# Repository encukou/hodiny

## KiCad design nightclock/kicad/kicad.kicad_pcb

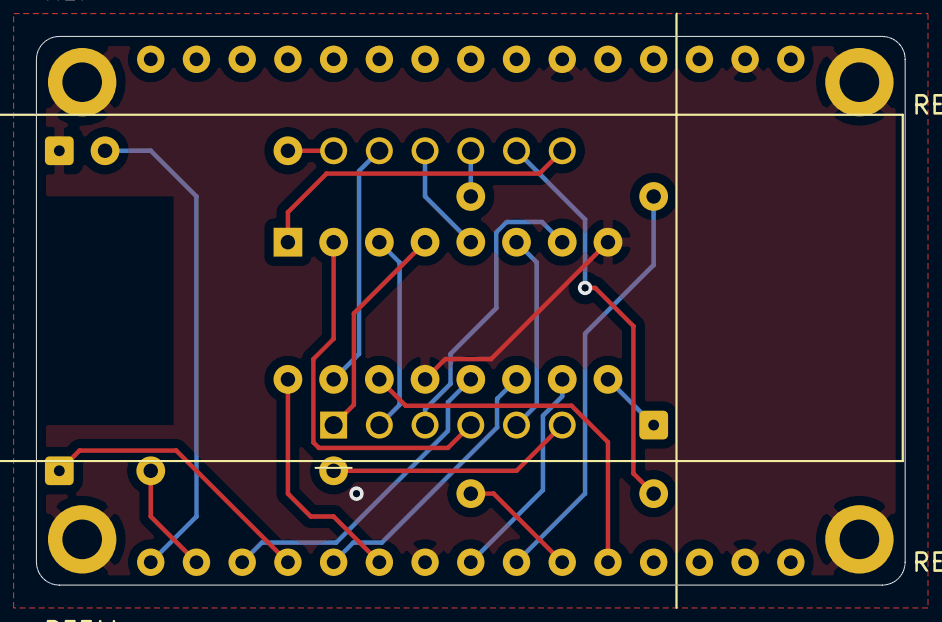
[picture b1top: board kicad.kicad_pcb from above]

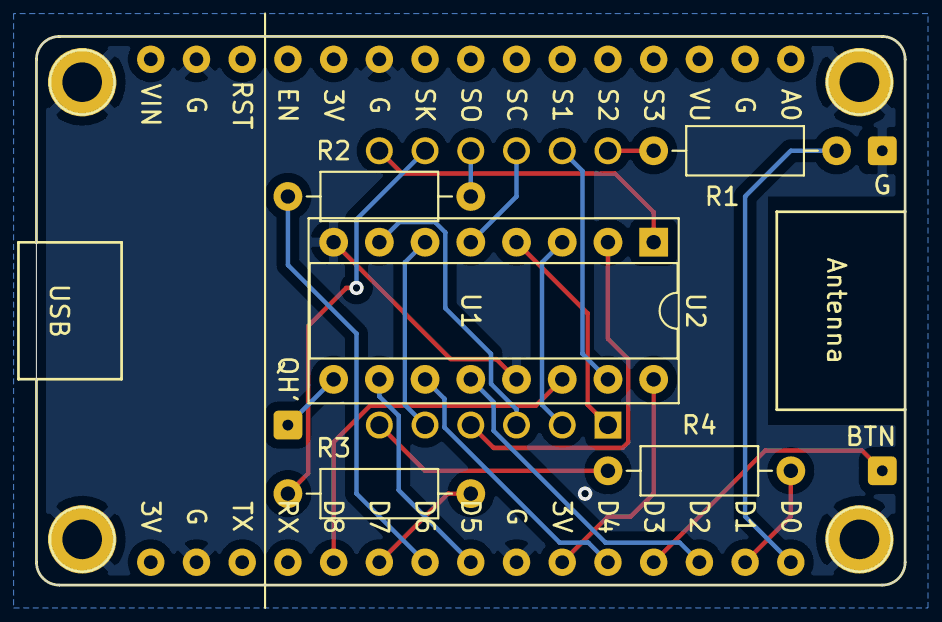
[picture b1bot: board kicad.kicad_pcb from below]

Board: 2 copper layers, 48.3 x 30.5 mm, 10 parts (8 on the bottom side), 24 nets.

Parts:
BTN: SolderWire-0.1sqmm_1x01_D0.4mm_OD1mm
G: SolderWire-0.1sqmm_1x01_D0.4mm_OD1mm
QH': SolderWire-0.1sqmm_1x01_D0.4mm_OD1mm
R1, R2, R3, R4: R; R_Axial_DIN0207_L6.3mm_D2.5mm_P10.16mm_Horizontal
U1: NodeMCU_1.0_(ESP-12E); NodeMCU1.0(12-E)
U2: 74HC595; DIP-16_W7.62mm_Socket
U3: CC56-12EWA; CA56-12EWA

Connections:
/3v3: U1.25, U2.16
/button: BTN.1, U1.27
/dig1: R1.1, U1.30
/dig2: R2.1, U1.22
/dig3: R3.1, U1.21
/dig4: R4.1, U1.29
/rclk: U1.28, U2.12
/ser: U1.20, U2.14
/srclk: U1.26, U2.11
/srclr': U1.23, U2.10
GND: G.1, U1.10, U1.14, U1.17, U1.24, U2.8, U2.13
unnamed: R1.2, U3.12
unnamed: R2.2, U3.9
unnamed: R3.2, U3.8
unnamed: R4.2, U3.6
unnamed: U2.1, U3.7
unnamed: U2.2, U3.4
unnamed: U2.3, U3.2
unnamed: U2.4, U3.1
unnamed: U2.5, U3.10
unnamed: U2.6, U3.5
unnamed: U2.7, U3.3
unnamed: QH'.1, U2.9
unnamed: U2.15, U3.11

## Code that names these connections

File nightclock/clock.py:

from machine import Pin
from time import sleep
import time
import network
import ntptime
from machine import idle

DST_START = 3, 28, 3
DST_END = 31, 10, 3

with open('settings.txt') as f:
    # The file settings.txt must have wifi and NTP config on 3 lines:
    SSID = f.readline().strip()
    PASSWORD = f.readline().strip()
    ntptime.host = f.readline().strip()

def cettime():
    # From https://forum.micropython.org/viewtopic.php?f=2&t=4034
    # Micropython esp8266
    # This code returns the Central European Time (CET) including daylight saving
    # Winter (CET) is UTC+1H Summer (CEST) is UTC+2H
    # Changes happen last Sundays of March (CEST) and October (CET) at 01:00 UTC
    # Ref. formulas : http://www.webexhibits.org/daylightsaving/i.html
    #                 Since 1996, valid through 2099
    year = time.localtime()[0]       #get current year
    HHMarch   = time.mktime((year,3 ,(31-(int(5*year/4+4))%7),1,0,0,0,0,0)) #Time of March change to CEST
    HHOctober = time.mktime((year,10,(31-(int(5*year/4+1))%7),1,0,0,0,0,0)) #Time of October change to CET
    now=time.time()
    if now < HHMarch :               # we are before last sunday of march
        cet=time.localtime(now+3600) # CET:  UTC+1H
    elif now < HHOctober :           # we are before last sunday of october
        cet=time.localtime(now+7200) # CEST: UTC+2H
    else:                            # we are after last sunday of october
        cet=time.localtime(now+3600) # CET:  UTC+1H
    return(cet)

def rot180(src):
    """Oh no, I built the thing upside down! Rotate in software"""
    a = bool(src & 0b10000000)
    b = bool(src & 0b01000000)
    c = bool(src & 0b00100000)
    d = bool(src & 0b00010000)
    e = bool(src & 0b00001000)
    f = bool(src & 0b00000100)
    g = bool(src & 0b00000010)
    p = bool(src & 0b00000001)
    return (d<<7) | (e<<6) | (f<<5) | (a<<4) | (b<<3) | (c<<2) | (g<<1) | p

digits = {
    n: rot180(b) for n, b in {
    0: 0b11111100,
    1: 0b01100000,
    2: 0b11011010,
    3: 0b11110010,
    4: 0b01100110,
    5: 0b10110110,
    6: 0b10111110,
    7: 0b11100000,
    8: 0b11111110,
    9: 0b11110110,
    "c": 0b10011100,
    "o": 0b00111010,
    "n": 0b00101010,
    "t": 0b00011110,
    "p": 0b11001110,
    "a": 0b11101110,
    " ": 0b00000000,
    "_": 0b00010000,
    "-": 0b00000010,
    "~": 0b10000000,
    "⠁": 0b10000000,
    "⠂": 0b01000000,
    "⠄": 0b00100000,
    "⠠": 0b00010000,
    "⠐": 0b00001000,
    "⠈": 0b00000100,
}.items()}

ser = Pin(15, Pin.OUT)  # D8
rclk = Pin(4, Pin.OUT)  # D2
srclk = Pin(2, Pin.OUT)  # D4
srclr_ = Pin(14, Pin.OUT)  # D5
button = Pin(0, Pin.IN)  # D3
digit_pins = [
    # Oh no, I built the thing upside down! Rhese are reversed.
    Pin(5, Pin.OUT),  # D1
    Pin(13, Pin.OUT),  # D7
    Pin(12, Pin.OUT),  # D6
    Pin(16, Pin.OUT),  # D0
]

rclk(0)
srclk(1)
srclr_(0)
srclr_(1)

def show_bytes(bytes):
    prev_pin = digit_pins[-1]
    for current_pin, byte in zip(digit_pins, bytes):
        rclk(0)
        for b in range(8):
            srclk(0)
            ser((byte >> b) & 1)
            srclk(1)
        prev_pin(1)
        rclk(1)
        current_pin(0)
        prev_pin = current_pin

def display_off():
    for pin in digit_pins:
        pin(1)

display_off()

def show_str(string):
    show_bytes(digits[c] for c in string)

wlan = network.WLAN(network.STA_IF)
wlan.active(True)
show_str("can-")
wlan.scan()
n_tries = 0
print('Connecting...')
while not wlan.isconnected():
    if n_tries % 100 == 0:
        wlan.connect(SSID, PASSWORD)
        idle()
    start = time.ticks_ms() # get millisecond counter
    sleep(0.1)
    show_str("⠁⠁⠁⠁⠁⠂⠄⠠⠐⠈"[n_tries % 10])
    n_tries += 1
print('Connected')

display_off()

def ntp_sync():
    print('NTP sync...')
    global NEXT_SYNC
    n_tries = 0
    while True:
        try:
            ntptime.settime()
            break
        except OSError:
            start = time.ticks_ms() # get millisecond counter
            while True:
                delta = time.ticks_diff(time.ticks_ms(), start)
                if delta > 1000:
                    break
                show_str("ntp" + "_-~"[n_tries % 3])
            n_tries += 1

    yr, mo, dy, hr, mn, sc, wday, yday = cettime()
    NEXT_SYNC = yr, mo, dy, hr + 1
    print('synced')

ntp_sync()
display_off()

while True:
    if not button():
        while True:
            yr, mo, dy, hr, mn, sc, wday, yday = localtime = cettime()
            if button():
                break
            digs = (
                digits[(hr // 10) % 10] | (sc & 1),
                digits[hr % 10],
                digits[(mn // 10) % 10] | 1,
                digits[mn % 10],
            )
            show_bytes(digs)
        display_off()
        if localtime > NEXT_SYNC:
            ntp_sync()
    idle()

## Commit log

2021-10-14 Initial commit of MicroPython clock
2021-10-14 Eliminate one shift register
2021-10-15 Switch pins & add settings.txt
2021-10-15 Add a KiCad schema/board
2021-11-12 Better connection sequence
2021-11-13 Adjust to the display (I built it upside-down...)
2021-11-13 Improve 3D model based on the first print
2021-11-13 Add some 3D-printing models
2022-01-05 Initial pomodoro clock
